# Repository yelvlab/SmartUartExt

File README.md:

# SmartUartExt
Webduino Smart Uart Extend Board
> PCB Project

## About:

SW : Kicad (5.1.4)-1

IC : WCH-CH340K

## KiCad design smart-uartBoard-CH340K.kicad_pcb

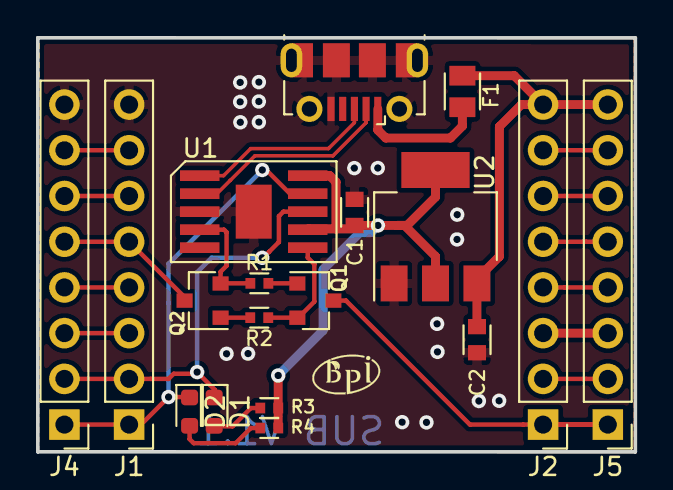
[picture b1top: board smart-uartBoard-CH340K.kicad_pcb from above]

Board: 2 copper layers, 33.2 x 23.0 mm, 20 parts (1 on the bottom side), 26 nets.

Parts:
C1, C2: 10uF; C0603
D1, D2: LED-R; LED_0603_1608Metric
F1: Fuse 500mA; R0805
J1, J4: Smart-Pin-2; Pin_Header_Straight_1x08_Pitch2.54mm
J2, J5: Smart-Pin-1; Pin_Header_Straight_1x08_Pitch2.54mm
J3: USB_B_Micro; USB_Micro-B_Molex-105017-0001
O1: BPI-LOGO; bpi-logo
O2: Webduino-Logo; webduino-logo
Q1, Q2: MMBT3904; SOT-23
R1, R2, R3, R4: 1K; R0402
U1: CH340K; ESSOP-10
U2: AMS1117-3.3; SOT-223-3_TabPin2

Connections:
+3V3: C1.2, R3.1, R4.1, U1.7, U1.10, U2.2
/00: J1.5, J4.5, Q2.3
/02: J1.6, J4.6
/3V3: J2.3, J5.3
/04: J1.4, J4.4
/05: J1.3, J4.3
/12: J2.6, J5.6
/13: J2.7, J5.7
/14: J2.5, J5.5
/15: J1.7, J4.7
/16: J2.4, J5.4
/AD: J2.2, J5.2
/DTR: Q2.2, R1.1, U1.4
/RST: J2.1, J5.1, Q1.3
/RTS: Q1.2, R2.1, U1.6
/RX: D1.1, J1.2, J4.2, U1.8
/RXD: D2.1, J1.1, J4.1, U1.9
/UD+: J3.3, U1.1
/UD-: J3.2, U1.2
GND: C1.1, C2.1, J1.8, J3.5, J3.6, J4.8, U1.0, U1.3, U2.1
unnamed: D1.2, R3.2
unnamed: D2.2, R4.2
unnamed: F1.2, J3.1
unnamed: Q1.1, R1.2
unnamed: Q2.1, R2.2
VCC: C2.2, F1.1, J2.8, J5.8, U2.3

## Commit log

2019-12-15 Init
